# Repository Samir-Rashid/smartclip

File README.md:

# smartclip
Intelligent wearable hairclip. A testbed for wearable computing such as health monitoring devices. Supports Tock OS and the Thread protocol.

* low cost ($5)
* low power (3µA)
  * up to 10 years of battery life
* operates without internet access
* open source foundation for secure medical devices

[image src](https://www.printplaygames.com/product/15mm-wood-discs/)

> 4. Medical Device Innovation and Assistive Technologies
> - Pathway 1: Improve existing medical devices and assistive technologies (e.g., enhancing usability and sustainability, improving affordability of assistive devices).
> - Pathway 2: Design new medical devices and assistive solutions (e.g., innovative devices addressing unmet healthcare needs, new assistive technologies for specific disabilities).

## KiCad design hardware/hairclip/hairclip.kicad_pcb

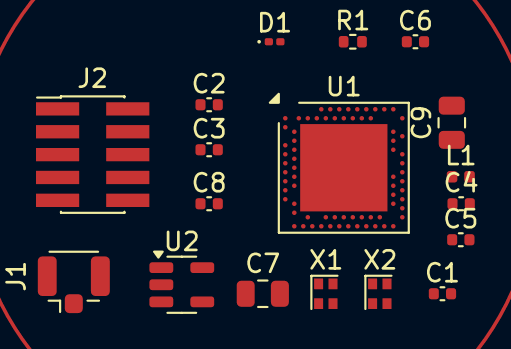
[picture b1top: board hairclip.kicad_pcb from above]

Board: 2 copper layers, 18 parts (0 on the bottom side), 10 nets, no tracks yet.

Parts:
C1, C2: 12pF; C_0402_1005Metric
C3: NC; C_0402_1005Metric
C4: 0pF5; C_0402_1005Metric
C5: 0pF8; C_0402_1005Metric
C6, C8: 100n; C_0402_1005Metric
C7, C9: 4u7; C_0805_2012Metric
D1: LED; LED_0201_0603Metric
J1: Conn_Coaxial_Small; U.FL_Hirose_U.FL-R-SMT-1_Vertical
J2: Conn_ARM_SWD_TagConnect_TC2030; PinHeader_2x05_P1.27mm_Vertical_SMD
L1: 4nH7; L_0402_1005Metric
R1: 220R; R_0402_1005Metric
U1: NRF52840-CKAA-R; Nordic_AQFN-73-1EP_7x7mm_P0.5mm
U2: MIC5365-3.3YD5; SOT-23-5
X1: 32MHz; Oscillator_SMD_Abracon_ASCO-4Pin_1.6x1.2mm
X2: 32kHz768; Oscillator_SMD_Abracon_ASCO-4Pin_1.6x1.2mm

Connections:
+3.3V: C6.1, C9.1, U1.B3 (VDD), U2.5 (VOUT)
+5V: C7.1, U2.1 (VIN), U2.3 (EN)
GND: C1.1, C2.1, C3.2, C4.2, C5.2, C6.2, C7.2, C8.2, C9.2, J2.5 (GND), R1.2, U1.C1 (VSS_PA), U2.2 (GND), X1.2, X1.4
unnamed: C4.1, L1.1
unnamed: D1.1 (K), R1.1
unnamed: J2.4 (SWCLK), U1.H2 (SWDCLK)
unnamed: C8.1, J2.3 (~RESET)
unnamed: C5.1, L1.2
unnamed: C2.2, U1.B9 (P0.00/XL1), X2.2
unnamed: C1.2, X2.1

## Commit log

2024-10-12 Add initial structure
2024-10-12 MCU power and decoupling
2024-10-12 add low speed oscillator
2024-10-13 Add high speed oscillator, antenna, LED, JTAG, Voltage regulator
2024-10-13 add initial pcb
2024-10-13 repo cleanup
2024-10-13 add readme images
2024-11-19 fix: improper image licensing
